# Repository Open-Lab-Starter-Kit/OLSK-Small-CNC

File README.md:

<div align="center"><h1 style=align="center">OLSK Small CNC V3</h1></div>

<div align="center"></div>
<div align="center"><i>Open Source CNC Milling machine - Small version - Open Lab Starter Kit</i></div>

<br>

Introduction
--

The OLSK Small CNC V3 is a desktop CNC milling machine with an innovative open-source tool changer, one of the first in an open-source machine.

The Assembly Manual
--

All OLSK machines are open source and have the BOM and necessary files available in this repository for replication. The assembly of parts is also documented in a workbook where each step contains a list of parts, tools and instruction remarks, following a logical order to provide a smooth assembly.

- **[Assembly Manual](https://open-lab-starter-kit.github.io/OLSK-Small-CNC/)**

Specifications V3
--

- machine external dimensions: W740mm x D960mm x H800mm (~H1600mm open door)
- working area: 400mm x 600mm x 150mm Width(X) x Depth(Y) x Height(Z)
- Automatic tool changer (capacity: 10 tools)
- Automatic tool measurement
- Automatic tool cleaning
- Coolant System
- Integrated liftable full-enclosed housing
- Flush-mounted 24V emergency stop
- Key Operated
- Universal bed (fixture clamping and vacuum)
- Closed Loop DC Servo Motors
- Belt decoupling on all axes
- Mounted touch screen
- Software: OLOS

Files
--

- **[CAD](cad)**
- **[Firmware](firmware)**
- **[Settings](settings)**
- **[BOM](OLSK_Small_CNC_V3-BOM.xlsx)**
- **[Wiring Schematic](OLSK_Small_CNC_V3_WiringSchematic.pdf)**

Author
--

OLSK Small CNC has been designed and built by **[InMachines Ingrassia GmbH](https://www.inmachines.net/)**.

<be>

Machine design:
- **[Daniele Ingrassia](https://www.linkedin.com/in/danieleingrassia/)**

PCB Design:
- **[Wilhelm Schütze](http://fabacademy.org/archives/2015/sa/students/schutze.wilhelm/index.html)**

The machine is part of the **[Open Lab Starter Kit (OLSK)](https://www.inmachines.net/open-lab-starter-kit)** group of open source digital fabrication machines.

OLSK is developed by **[InMachines Ingrassia GmbH](https://www.inmachines.net/)** for the **[Dtec project](https://dtecbw.de/home/forschung/hsu/projekt-fabcity)** at **[Fab City Hamburg](https://www.fabcity.hamburg/en/)**.

OLSK Partners:
<br><br>

Contact
--

- daniele@inmachines.net
- [https://www.inmachines.net/](https://www.inmachines.net/)

License
--

Hardware design, CAD and PCB files, BOM, settings and other technical or design files are released under the following license:

- CERN Open Hardware Licence Version 2 Weakly Reciprocal - **[CERN-OHL-W](LICENSE_CERN_OHL_W_V2.txt)**

Assembly manual, pictures, videos, presentations, description text and other type of media are released under the following license:

- Creative-Commons-Attribution-ShareAlike 4.0 International - **[CC BY-SA 4.0](LICENSE_CC_BY_SA_4.0.txt)**

Copyright
--

- Daniele Ingrassia, InMachines Ingrassia GmbH

- Tobias Redlich, Helmut-Schmidt-Universität/Universität der Bundeswehr Hamburg

Previous Version
--

The previous versions of OLSK machines will always be available.

**[OLSK Small CNC Milling Machine V2](OLSK_Small_CNC_V1)**
<br> <br>

**[OLSK Small CNC Milling Machine V1](OLSK_Small_CNC_V1)**
<br> <br>

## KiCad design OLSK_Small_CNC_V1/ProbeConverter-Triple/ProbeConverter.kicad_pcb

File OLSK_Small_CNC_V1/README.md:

<div align="center"><h1 style=align="center">OLSK Small CNC V1</h1></div>

<div align="center"></div>
<div align="center"><i>Open Source CNC Milling machine - Small version - Open Lab Starter Kit</i></div>

<br>

Introduction
--

The OLSK Small CNC V1 is a desktop CNC milling machine with innovative, compact and sturdy design. The bed, with a milling volume of 600 x 400 x 170 mm (X x Y x Z), features a powerful vacuum system to hold plates without clamping. It is also adapted to fit different international unit systems to allow the fixation of different vices and other accessories. The Z-axis is compact, with a minimum distance to the X-axis linear guides, giving the milling more stability and sturdiness. The linear guides from the Y and Z axis are protected against material chips. The machine also includes a Z height tool sensor and homing with inductive sensors.

Learning by Making
--

The OLSK Small CNC V1 can be offered as an assembly kit with all the necessary parts to build it, saving the user the time to produce and procure the parts. Building a machine provided the opportunity to understand how the machine operates from the inside and the function of each part. This machine can also be built with the help of a workshop lead by the InMachines team, as unique learning experience for small groups, resulting in a full operational CNC milling machine for your makerspace.

The Assembly Workbook
--

All OLSK machines are open source and have the BOM and necessary files available in this repository for replication. The assembly of parts is also documented in a workbook where each step contains a list of parts, tools and instruction remarks, following a logic order to provide a smooth assembly.

Specifications V1
--

- milling volume: 600 x 400 x 170 mm
- frame: solid aluminum
- electronic box frame: 20 x 2m mm aluminum profiles
- electronic box housing: aluminum composite
- bed: CNC milled aluminum
- motion: ball screws 12 and 16 mm
- guides: 15 mm linear rails
- motors: stepper motor NEMA 24
- firmware: grbl-LPC
- additional: modular vacuum bed and coolant system
- Z height tool sensor
- bed compatible with different international unit systems

Files
--

- **[Assembly Workbook](OLSK_Small_CNC_V1_Workbook.pdf)**
- **[Wiring Schematic](OLSK_Small_CNC_V1_Wiring_Schematic.pdf)**
- **[BOM](OLSK_Small_CNC_V1_BOM.pdf)**
- **[CAD](cad)**
- **[Firmware](firmware)**
- **[Sensor PCB](ProbeConverter-Triple)**
- **[Fusion 360 machine settings](machine_settings)**
- **[Z tool Sensor detection](Z_Tool_Probe.nc)**

Author
--

OLSK Small CNC has been designed and built by **[InMachines Ingrassia GmbH](https://www.inmachines.net/)**.

<br>

Machine design:
- **[Daniele Ingrassia](https://www.linkedin.com/in/danieleingrassia/)**

The machine is part of the **[Open Lab Starter Kit (OLSK)](https://www.inmachines.net/open-lab-starter-kit)** group of open source digital fabrication machines.

OLSK is developed by **[InMachines Ingrassia GmbH](https://www.inmachines.net/)** for the **[Dtec project](https://dtecbw.de/home/forschung/hsu/projekt-fabcity)** at **[Fab City Hamburg](https://www.fabcity.hamburg/en/)**.

OLSK Partners:
<br><br>

Contact
--

- daniele@inmachines.net
- [https://www.inmachines.net/](https://www.inmachines.net/)

License
--

Hardware design, CAD and PCB files, BOM, settings and other technical or design files are released under the following license:

- CERN Open Hardware Licence Version 2 Weakly Reciprocal - **[CERN-OHL-W](LICENSE_CERN_OHL_W_V2.txt)**

Assembly manual, pictures, videos, presentations, description text and other type of media are released under the following license:

- Creative-Commons-Attribution-ShareAlike 4.0 International - **[CC BY-SA 4.0](LICENSE_CC_BY_SA_4.0.txt)**

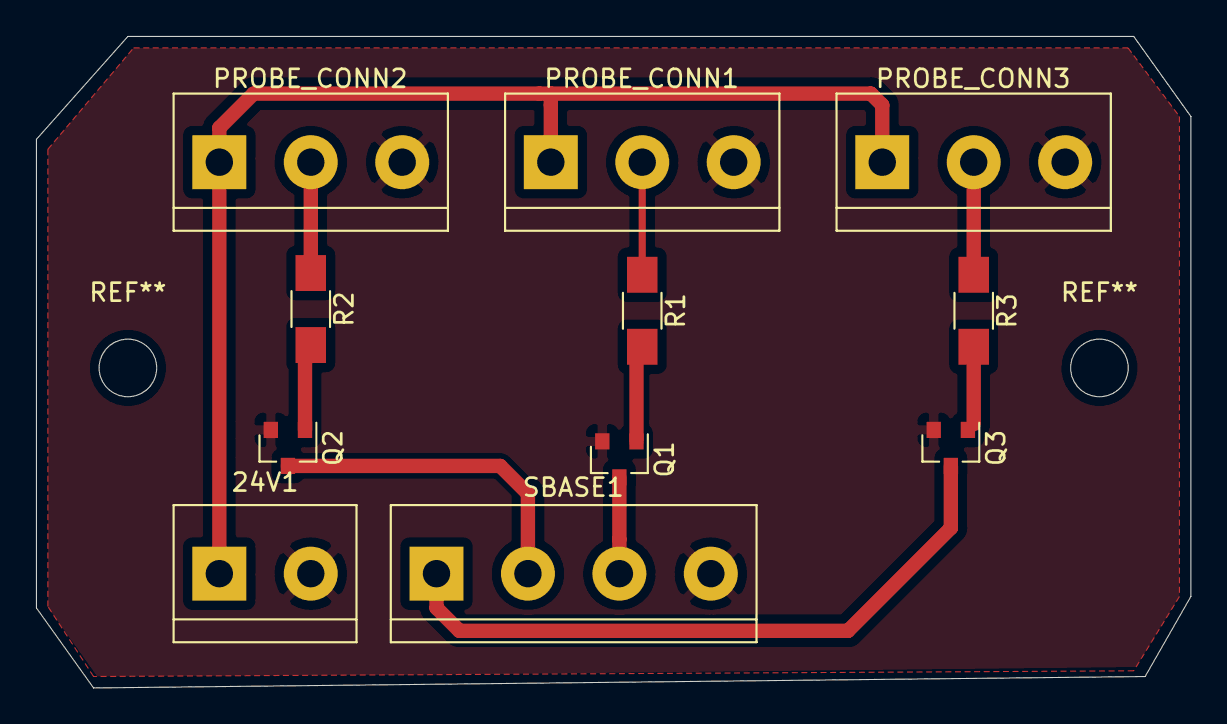
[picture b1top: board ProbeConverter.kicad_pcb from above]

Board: 2 copper layers, 64.1 x 36.2 mm, 11 parts (0 on the bottom side), 11 nets.

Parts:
24V1: Screw_Terminal_01x02; TerminalBlock_bornier-2_P5.08mm
PROBE_CONN1, PROBE_CONN2, PROBE_CONN3: Screw_Terminal_01x03; TerminalBlock_bornier-3_P5.08mm
Q1, Q2, Q3: BC846; SOT-23
R1, R2, R3: 10K; R_1206
SBASE1: Screw_Terminal_01x04; TerminalBlock_bornier-4_P5.08mm

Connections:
24V: 24V1.1, PROBE_CONN1.1, PROBE_CONN2.1, PROBE_CONN3.1
GND: 24V1.2, PROBE_CONN1.3, PROBE_CONN2.3, PROBE_CONN3.3, Q1.2, Q2.2, Q3.2, SBASE1.4
unnamed: PROBE_CONN1.2, R1.1
unnamed: PROBE_CONN2.2, R2.1
unnamed: PROBE_CONN3.2, R3.1
unnamed: Q1.1, R1.2
unnamed: Q2.1, R2.2
unnamed: Q3.1, R3.2
SIGNAL1: Q1.3, SBASE1.3
SIGNAL2: Q2.3, SBASE1.2
SIGNAL3: Q3.3, SBASE1.1

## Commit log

2022-12-24 Update README.md
    added license
2022-12-24 Update README.md
    updated license setcion
2022-12-24 updated author
2022-12-24 added inmachines logo
2022-12-24 updated inmachines logo
2022-12-24 updated partners logos
2022-12-24 modified readme
2022-12-24 test blank in links
2022-12-24 test blank html
2022-12-24 removed blank
2022-12-24 added contacts
2022-12-24 updated authors
2022-12-24 added picture, specs and CAD files
2022-12-24 updated specs
2022-12-24 added V1
2023-01-11 Update README.md
    added introduction
2023-01-12 added images
2023-01-12 Update README.md
    added text and images
2023-01-12 Update README.md
    added firmware and pcb
2023-01-12 upload pcb anf firmware files
2023-01-12 upload license
2023-01-12 removed firmware
2023-01-12 upload firmware
2023-01-12 upload workbook and wiring schematic
2023-01-12 upload BOM
2023-01-12 Update README.md
    added bom, workbook and wiring schematic
2023-01-12 fix wiring schematic file name
2023-01-12 Update README.md
    fix file name
2023-01-12 updated workbook
2023-03-29 Fusion 360 machine settings
2023-03-29 Update README.md
    added machine settings
2023-03-29 Update README.md
    fixed link
2023-03-29 update folder
2023-03-29 upload z tool probe
2023-03-29 upload versions of wiring
2023-03-29 Update README.md
    update wiring schematic link
2023-10-20 Create V1 Folder
2023-10-20 add CAD
2023-10-20 add firmware
2023-10-20 add workbook
2023-10-20 added media
2023-10-26 add media
2023-10-26 media change
2023-10-26 update media
2024-03-05 update wiring
2024-10-06 added CAD for workshop, Fusion 360 version
2024-10-06 added CAD for workshop, step version
2025-03-11 Upload Assembly Manual
2025-03-13 Update Assembly Manual
2025-03-13 Move V2 to folder
2025-03-13 Update V3
2025-03-13 Upload cad
2025-03-13 Upload images
2025-05-05 Add REUSE metadata
    Added .reuse/dep5 file to declare licenses and copyright metadata
